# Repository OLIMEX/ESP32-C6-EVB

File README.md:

# ESP32-C6-EVB
ESP32-C6-EVB is evaluation board with WiFi6, Bluetooth 5LE and Zigbee Matter support

Product page: https://www.olimex.com/Products/IoT/ESP32-C6/ESP32-C6-EVB/open-source-hardware
## License
* Hardware is released under CERN OHL v1.2 license
* Software is released under GPL3 License
* Documentation is released under CC BY-SA 3.0

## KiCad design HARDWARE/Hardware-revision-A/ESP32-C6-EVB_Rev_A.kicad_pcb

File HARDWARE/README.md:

# ESP32-C6-EVB

Design files for Olimex ESP32-C6-EVB. Board is made with KiCAD. This is an open-source hardware project, released under CERN OHL v1.2 license.

STL files for a 3d printed case can be found in directory "3D printed case". All STL files were created with Fusion 360.

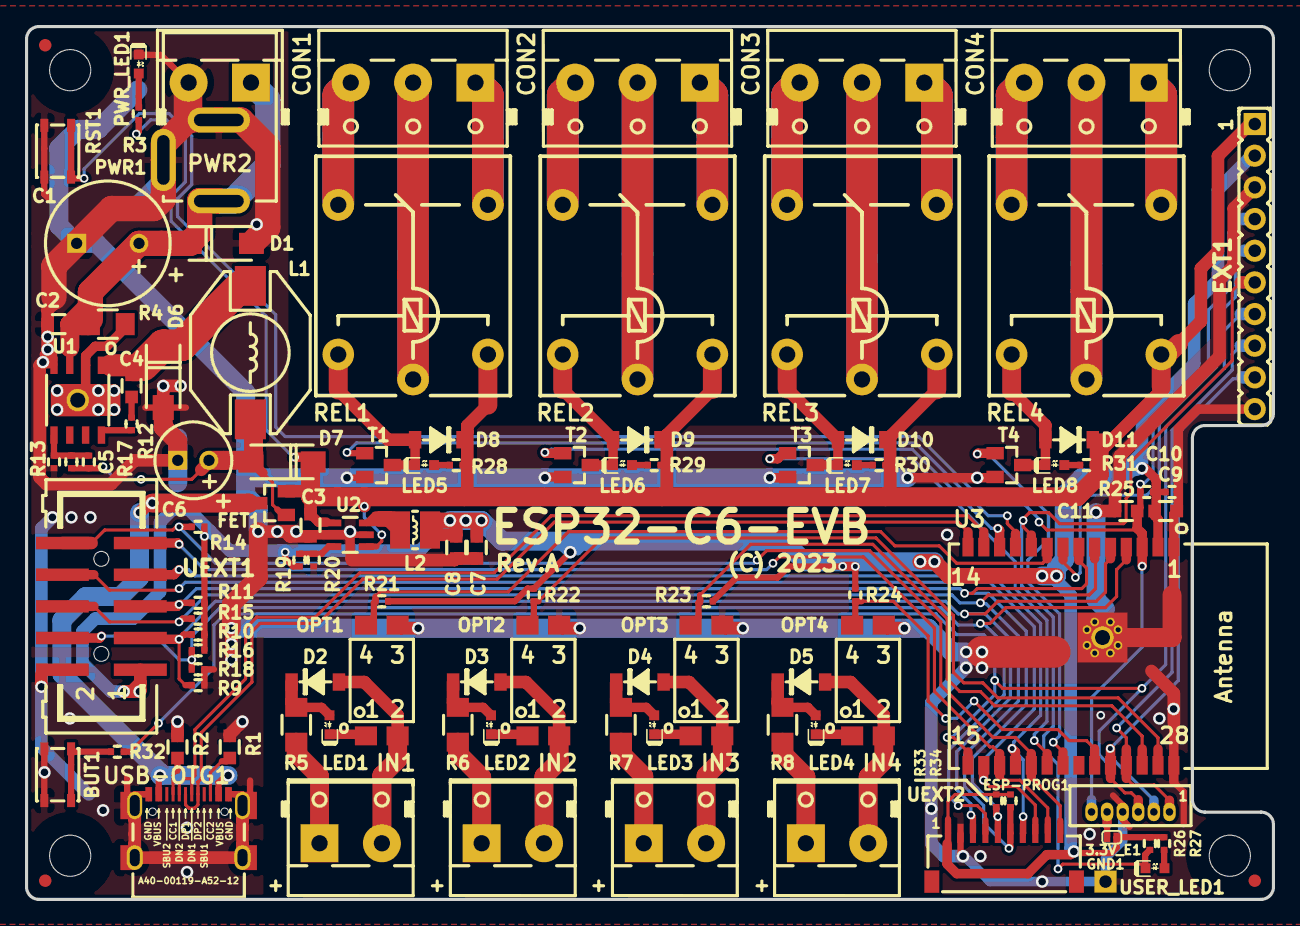
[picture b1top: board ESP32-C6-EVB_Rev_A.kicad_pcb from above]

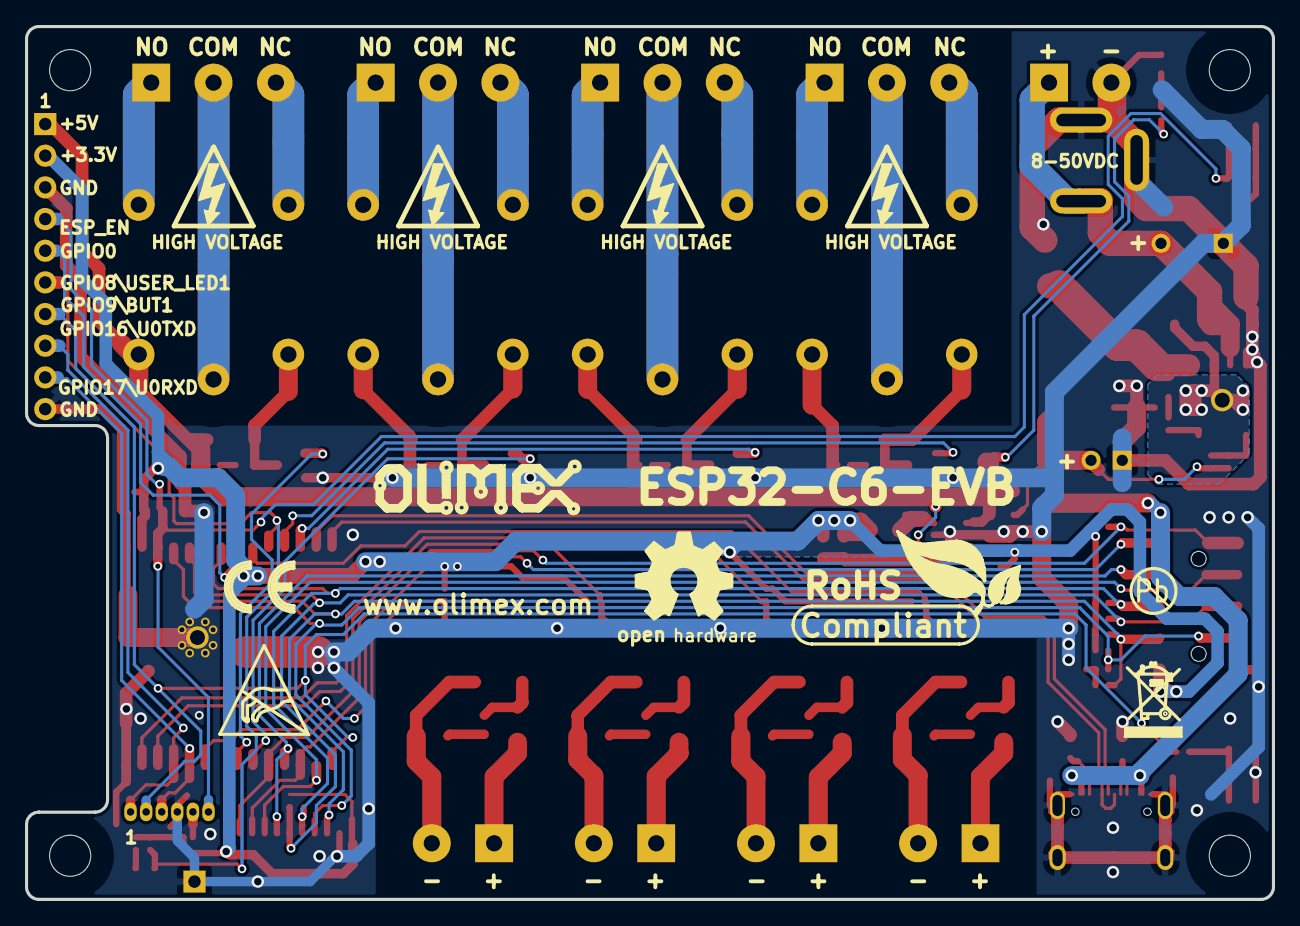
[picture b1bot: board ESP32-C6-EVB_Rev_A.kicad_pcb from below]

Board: 2 copper layers, 100.0 x 70.0 mm, 121 parts (11 on the bottom side), 79 nets.

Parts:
3.3V_E1: Opened; SJ_1_SMALLER
BUT1: YTS-A016-X
C1: 100uF/63V/20%/10x13MM/Low_ESR/RM5; CPOL-RM5mm_10.0x16.0mm_PTH
C2, C4: 100nF/100V/10%/X7R/C0603; C_0603_5MIL_DWS
C3, C7, C8, C9: 22uF/6.3V/20%/X5R/C0603; C_0603_5MIL_DWS
C5: 12pF/50V/5%/COG/C0402; C_0402_5MIL_DWS
C6: 470uF/10V/20%/Low_ESR/RM2.5/6.0x11mm; CPOL-RM2.5mm_6.3x11mm_PTH
C10: 100nF/10V/10%/X7R/C0402; C_0402_5MIL_DWS
C11: 1uF/10V/10%/X5R/C0603; C_0603_5MIL_DWS
CON1, CON2, CON3, CON4: DG306-5.0-3P; TB3-DG306-5.0_3P
D1: SMAJ58A/SMA; SMA-KA
D2, D3, D4, D5, D8, D9, D10, D11: 1N4148W(SOD-123); SOD-123_1C-2A_KA
D6: SS310/SMA; SMA-KA
D7: 1N5822/SS34/SMA; SMA-KA
ESP-PROG1: NA(WU06S); WU06S
EXT1: NA(HN1x10); HN1x10
FET1: WPM2015-3/TR; SOT23
FID1, FID2, FID3: Fiducial; Fiducial1x3
GND1: TESTPAD; TEST_PAD40x70_SQUARE
IN1, IN2, IN3, IN4: DG306-5.0-2P; TB2-DG306-5.0_2P
L1: 33uH/2.1A/DCR=0.1R/20%/DBS135(PD3316MT330); DBS135
L2: 2.2uH/1.5A/DCR=72mR/20%/3.00x3.00x1.50mm/CD32(NR3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; CD32
LED1, LED2, LED3, LED4: LED/RED/0603; LED_0603_KA
LED5, LED6, LED7, LED8: LED/GREEN/0603; LED_0603_KA
Logo_OLIMEX_TB: Logo_OLIMEX_TB
MH1, MH2, MH3, MH4: Mounting_Hole_NPTH; Mounting_Hole_Drill-3.3mm_Clerance-7mm
OPT1, OPT2, OPT3, OPT4: PC817CS_CYPC817(C-TP2); H11A817C_SMD(PC817X3NIP06)_FP
PWR1: PWRJ-2mm(YDJ-1134); PWRJ-2mm(YDJ-1136)
PWR2: NA(DG306-5.0-2P); TB2-DG306-5.0_2P
PWR_LED1: LED/RED/0603; LED_0603_KA
R1, R2: 5.1k/R0603; R_0603_5MIL_DWS
R3, R11, R15, R27, R28, R29, R30, R31: 2.2k/R0402; R_0402_5MIL_DWS
R4: 0.03R/1%/R1206; R_1206_5MIL_DWS
R5, R6, R7, R8: 3.9k/R1206; R_1206_5MIL_DWS
R9, R10, R18: NA/R0402; R_0402_5MIL_DWS
R12: 4.7R/R0402; R_0402_5MIL_DWS
R13: 5.23k/1%/R0402; R_0402_5MIL_DWS
R14, R16, R25, R26: 10k/R0402; R_0402_5MIL_DWS
R17: 30.1k/1%/R0402; R_0402_5MIL_DWS
R19: 220k/R0402; R_0402_5MIL_DWS
R20: 49.9k/1%/R0402; R_0402_5MIL_DWS
R21, R22, R23, R24: 47k/R0402; R_0402_5MIL_DWS
R32: 100R/R0402; R_0402_5MIL_DWS
R33, R34: NA(2.2k/R0402); R_0402_5MIL_DWS
REL1, REL2, REL3, REL4: RAS-0515; Relay_RAS-05-15
RST1: YTS-A016-X
Sign_Antistatic: Sign_Antistatic
Sign_CE: CE_Sign
Sign_High_Voltage: Sign_High_Voltage
Sign_High_Voltage#2, Sign_High_Voltage#3, Sign_High_Voltage#4: Sign_High_Voltage
Sign_OSHW_8x8: Sign_OSHW_8x8
Sign_PB-Free: Sign_PB-Free
Sign_RecycleBin_1: Sign_RecycleBin_1
Sign_RoHS_1: Sign_RoHS_1
T1, T2, T3, T4: LMUN2235LT1G(SOT-23); SOT23
U1: TX4138(ESOIC-8); ESOIC-8
U2: SY8089AAAC(SOT23-5); SOT-23-5
U3: ESP32-C6-WROOM-1-N4; ESP32-C6-WROOM-1-xx-UNIVERSAL_MODULE
UEXT1: P-B-V-10-LF; GBH-254-SMT-10
UEXT2: SM10B-SRSS-TB
USB-OTG1: USB-C-16P-F(A40-00119-A52-12); USB2.0_TYPE-C(A40-00119-A52-12)
USER_LED1: LED/GREEN/0603; LED_0603_KA

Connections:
+3.3V: 3.3V_E1.2, C7.1, C8.1, C9.1, C10.2, EXT1.2, L2.2, R10.1, R11.1, R14.1, R15.1, R16.1, R19.2, R21.2, R22.2, R23.2, R24.2, R25.1, R26.1, R27.1, R33.1, R34.1, U3.2, UEXT1.1, UEXT2.1
+5V: C3.1, D7.1, D8.1, D9.1, D10.1, D11.1, EXT1.1, FET1.2, R3.2, R28.2, R29.2, R30.2, R31.2, REL1.1, REL2.1, REL3.1, REL4.1, U2.1, U2.4
+5V_EXT: C5.1, C6.1, D7.2, FET1.1, L1.2, R17.1
+5V_USB: FET1.3, USB-OTG1.A4, USB-OTG1.A9, USB-OTG1.B4, USB-OTG1.B9
/CC1: R2.2, USB-OTG1.A5
/CC2: R1.2, USB-OTG1.B5
/ESP_EN: C11.1, ESP-PROG1.6, EXT1.4, R25.2, RST1.2, U3.3
/GPIO0: EXT1.5, U3.8
/GPIO1\In1: OPT1.4, R21.1, U3.9
/GPIO2\In2: OPT2.4, R22.1, U3.27
/GPIO3\In3: OPT3.4, R23.1, U3.26
/GPIO4\LP_UART_RXD: R16.2, R18.2, U3.4, UEXT1.4, UEXT2.4
/GPIO5\LP_UART_TXD: R9.2, R10.2, U3.5, UEXT1.3, UEXT2.3
/GPIO6\LP_I2C_SDA: R15.2, R34.2, U3.6, UEXT1.6, UEXT2.6
/GPIO7\LP_I2C_SCL: R11.2, R33.2, U3.7, UEXT1.5, UEXT2.5
/GPIO8\USER_LED1: EXT1.6, R26.2, U3.10, USER_LED1.1
/GPIO9\BUT1: ESP-PROG1.2, EXT1.7, R32.1, U3.15
/GPIO10\REL1: T1.1, U3.11
/GPIO11\REL2: T2.1, U3.12
/GPIO12\USB_D-: U3.13, USB-OTG1.A7, USB-OTG1.B7
/GPIO13\USB_D+: U3.14, USB-OTG1.A6, USB-OTG1.B6
/GPIO15\In4: OPT4.4, R24.1, U3.23
/GPIO16\U0TXD: ESP-PROG1.1, EXT1.8, U3.25
/GPIO17\U0RXD: ESP-PROG1.3, EXT1.9, U3.24
/GPIO18\SPI2D(MOSI)\SDIO_CMD: U3.16, UEXT1.8, UEXT2.8
/GPIO19\SPI2CLK(CLK)\SDIO_CLK: U3.17, UEXT1.9, UEXT2.9
/GPIO20\SPI2Q(MISO)\SDIO_DATA0: U3.18, UEXT1.7, UEXT2.7
/GPIO21\SPI2CS0(CS#)\SDIO_CD: R14.2, U3.19, UEXT1.10, UEXT2.10
/GPIO22\REL3: T3.1, U3.20
/GPIO23\REL4: T4.1, U3.21
/ILIM: R4.1, U1.2, U1.9
/VIN: C1.1, C2.1, D1.1, PWR1.+, PWR2.1, R4.2, U1.3
GND: BUT1.2, C1.2, C2.2, C3.2, C6.2, C7.2, C8.2, C9.2, C10.1, C11.2, D1.2, D6.2, ESP-PROG1.4, EXT1.3, EXT1.10, GND1.1, OPT1.3, OPT2.3, OPT3.3, OPT4.3, PWR1.-, PWR2.2, PWR_LED1.1, R1.1, R2.1, R9.1, R13.2, R18.1, R20.2, RST1.1, T1.2, T2.2, T3.2, T4.2, U1.4, U2.2, U3.1, U3.28, U3.29, UEXT1.2, UEXT2.2, USB-OTG1.0, USB-OTG1.A1, USB-OTG1.A12, USB-OTG1.B1, USB-OTG1.B12
unnamed: 3.3V_E1.1, ESP-PROG1.5
unnamed: BUT1.1, R32.2
unnamed: C4.1, D6.1, L1.1, U1.1
unnamed: C4.2, R12.2
unnamed: C5.2, R13.1, R17.2, U1.5
unnamed: CON1.1, REL1.NO0
unnamed: CON1.2, REL1.COM0
unnamed: CON1.3, REL1.NC0
unnamed: CON2.1, REL2.NO0
unnamed: CON2.2, REL2.COM0
unnamed: CON2.3, REL2.NC0
unnamed: CON3.1, REL3.NO0
unnamed: CON3.2, REL3.COM0
unnamed: CON3.3, REL3.NC0
unnamed: CON4.1, REL4.NO0
unnamed: CON4.2, REL4.COM0
unnamed: CON4.3, REL4.NC0
unnamed: D2.1, LED1.2, R5.2
unnamed: D2.2, IN1.2, OPT1.2
unnamed: D3.1, LED2.2, R6.2
unnamed: D3.2, IN2.2, OPT2.2
unnamed: D4.1, LED3.2, R7.2
unnamed: D4.2, IN3.2, OPT3.2
unnamed: D5.1, LED4.2, R8.2
unnamed: D5.2, IN4.2, OPT4.2
unnamed: D8.2, LED5.1, REL1.2, T1.3
unnamed: D9.2, LED6.1, REL2.2, T2.3
unnamed: D10.2, LED7.1, REL3.2, T3.3
unnamed: D11.2, LED8.1, REL4.2, T4.3
unnamed: IN1.1, R5.1
unnamed: IN2.1, R6.1
unnamed: IN3.1, R7.1
unnamed: IN4.1, R8.1
unnamed: L2.1, U2.3
unnamed: LED1.1, OPT1.1
unnamed: LED2.1, OPT2.1
unnamed: LED3.1, OPT3.1
unnamed: LED4.1, OPT4.1
unnamed: LED5.2, R28.1
unnamed: LED6.2, R29.1
unnamed: LED7.2, R30.1
unnamed: LED8.2, R31.1
unnamed: PWR_LED1.2, R3.1
unnamed: R12.1, U1.8
unnamed: R19.1, R20.1, U2.5
unnamed: R27.2, USER_LED1.2

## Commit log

2023-07-04 Update
    License
2023-07-04 Update
    Schematics
2023-07-04 Update
    Schematic export and demo
2023-08-04 Update
    Manual
2023-10-11 Adding STL files for 3d printed case
2023-10-11 updating names on STL files to match board name
2024-07-01 Update
    Dimensions
2026-04-28 New demo
    Arduino demo for relays, optocoupler inputs, button, user LED.
2026-04-28 Feature update
    Added esphome and platformio configs
2026-04-28 Added new Arduino demo
    Board control via serial via commands

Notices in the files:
HARDWARE/Hardware-revision-A/ESP32-C6-EVB_Rev_A.kicad_pcb:
(C) 2023
